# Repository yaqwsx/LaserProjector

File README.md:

# LaserProjector
Fancy driver for cheap Chinese laser galvos based on ESP32

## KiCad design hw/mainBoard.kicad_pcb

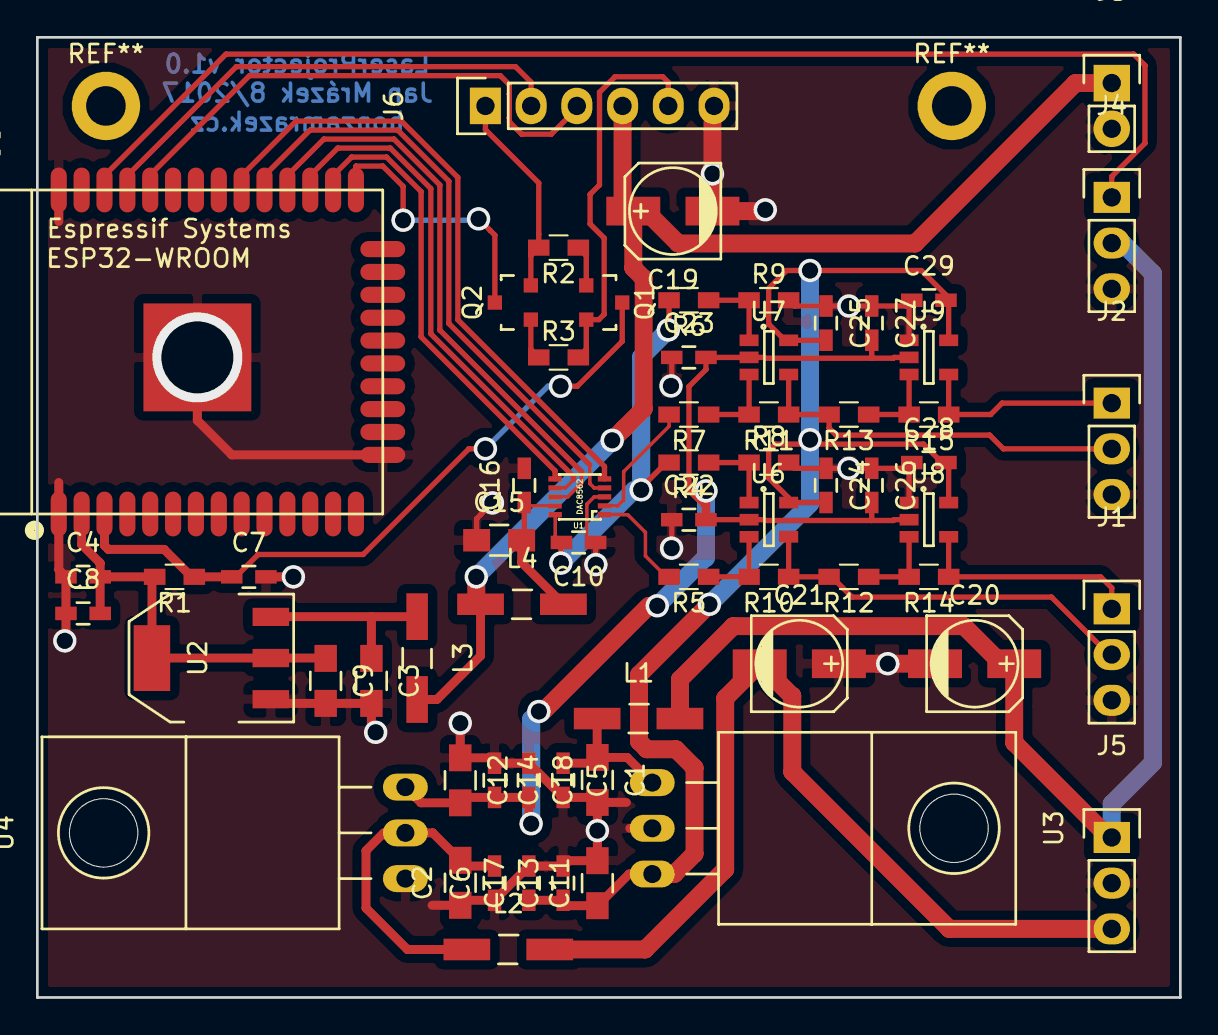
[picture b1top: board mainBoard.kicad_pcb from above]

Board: 2 copper layers, 63.5 x 53.3 mm, 65 parts (0 on the bottom side), 38 nets.

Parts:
C1, C2, C3, C9, C11, C12, C15: 10u; C_0805_HandSoldering
C4: 470n; C_0603_HandSoldering
C5, C6, C8, C13, C14, C16, C22, C23, C24, C25, C26, C27, C28, C29: 100n; C_0603_HandSoldering
C7, C17, C18: 1n; C_0603_HandSoldering
C10: 150nF; C_0603_HandSoldering
C19, C20, C21: 120u; c_elec_5x5.7
J1: Y; Pin_Header_Straight_1x03
J2: X; Pin_Header_Straight_1x03
J3: PWR_5; Pin_Header_Straight_1x02
J4: LASER; Pin_Header_Straight_1x03
J5: PWR_15; Pin_Header_Straight_1x03
J6: FTDI; Pin_Header_Straight_1x06
L1, L2, L3, L4: 33uH; Choke_SMD_1206_Handsoldering
Q1, Q2: BC817; SOT-23
R1, R2, R3, R4, R5, R6, R7: 10k; R_0603_HandSoldering
R8, R9, R10, R11, R12, R13, R14, R15: 20k; R_0603_HandSoldering
U1: DAC8562; VSSOP10
U2: AP1117; SOT-223
U3: LM7809CT; TO-220_Neutral123_Horizontal
U4: LM7909CT; TO-220_Neutral123_Horizontal
U5: ESP32-WROOM
U6, U7, U8, U9: MIC920; SOT-23-5

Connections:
+3V3: C4.2, C8.2, C9.1, R1.2, U2.2, U2.4, U5.2
+5V: C19.1, J3.1, J6.4, L3.2, L4.1
+9VA: C11.1, C13.1, C17.1, C24.2, C25.2, C28.2, C29.2, U3.3, U6.5, U7.5, U8.5, U9.5
+15V: C20.1, J4.2, J5.1, L1.2
-9VA: C12.2, C14.2, C18.2, C22.2, C23.2, C26.2, C27.2, U4.3, U6.2, U7.2, U8.2, U9.2
-15V: C21.2, J5.3, L2.2
BOOT: Q2.3, U5.25
CLR: U1.5, U5.30
DATA: U1.8, U5.28
DTR: J6.1, Q2.2, R2.2
EN: C7.1, Q1.3, R1.1, U5.3
GND: C1.2, C2.1, C3.2, C4.1, C5.2, C6.1, C7.2, C8.1, C9.2, C10.1, C11.2, C12.1, C13.2, C14.1, C15.1, C16.2, C17.2, C18.1, C19.2, C20.2, C21.1, C22.1, C23.1, C24.1, C25.1, C26.1, C27.1, C28.1, C29.1, J1.3, J2.3, J3.2, J4.3, J5.2, J6.6, R8.2, R9.2, U1.3, U2.1, U3.2, U4.1, U5.1, U5.15, U5.38, U5.39, U8.1, U9.1
LASER: J4.1, U5.36
LDAC: U1.4, U5.29
unnamed: C1.1, C5.1, L1.1, U3.1
unnamed: C2.2, C6.2, L2.1, U4.2
unnamed: C3.1, L3.1, U2.3
unnamed: C15.2, C16.1, L4.2, U1.9
unnamed: Q1.1, R2.1
unnamed: Q2.1, R3.1
unnamed: R4.1, R8.1, U6.1
unnamed: R6.1, R9.1, U7.1
unnamed: R5.1, R10.2, U6.3
unnamed: R7.1, R11.2, U7.3
unnamed: R12.1, R14.2, U8.3
unnamed: R13.1, R15.2, U9.3
RTS: J6.5, Q1.2, R3.2
RX: J6.2, U5.35
SCK: U1.7, U5.27
SIG_GROUND: C10.2, R4.2, R6.2, U1.10
SYNC: U1.6, U5.26
TX: J6.3, U5.34
XNEG: J2.1, R15.1, U9.4
XPOS: J2.2, R11.1, R13.2, U7.4
XSIG: R7.2, U1.2
YNEG: J1.1, R14.1, U8.4
YPOS: J1.2, R10.1, R12.2, U6.4
YSIG: R5.2, U1.1

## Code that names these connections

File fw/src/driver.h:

#pragma once

#include <driver/dac.h>
#include <driver/gpio.h>
#include <driver/spi_master.h>

extern "C" {
    #include <soc/spi_struct.h>
    #include <soc/spi_reg.h>

    typedef struct {
        spi_device_t *device[ 3 ];
        intr_handle_t intr;
        spi_dev_t *hw;
        spi_transaction_t *cur_trans;
        int cur_cs;
        lldesc_t *dmadesc_tx;
        lldesc_t *dmadesc_rx;
        bool no_gpio_matrix;
        int dma_chan;
        int max_transfer_sz;
    } spi_host_t;

    struct spi_device_t {
        QueueHandle_t trans_queue;
        QueueHandle_t ret_queue;
        spi_device_interface_config_t cfg;
        spi_host_t *host;
    };
}

struct IntDacDriver {
    IntDacDriver( gpio_num_t laserPin )
        : _lPin( laserPin )
    { }

    ~IntDacDriver() {
        stop();
    }

    void start() {
        dac_output_enable( DAC_CHANNEL_1 ); // GPIO 25
        dac_output_enable( DAC_CHANNEL_2 ); // GPIO 26
        gpio_set_direction( _lPin, GPIO_MODE_OUTPUT );
        gpio_set_level( _lPin, 0 );
    }

    void stop() {
        gpio_set_level( _lPin, 0 );
    }

    void show( ImgPoint p ) {
        dac_output_voltage( DAC_CHANNEL_1, 128 + ( p.x / 255 ) );
        dac_output_voltage( DAC_CHANNEL_2, 128 + ( p.y / 255 ) );
        gpio_set_level( _lPin, p.l > 0 );
    }

    gpio_num_t _lPin;
};

struct Dac8562Driver {
    Dac8562Driver( gpio_num_t din, gpio_num_t sck, gpio_num_t sync,
        gpio_num_t clr, gpio_num_t ldac, gpio_num_t laserPin )
    : _ldac( ldac ),
      _lPin( laserPin )
    {
        gpio_set_direction( clr, GPIO_MODE_OUTPUT );
        gpio_set_level( clr, 1 );

        gpio_set_direction( _ldac, GPIO_MODE_OUTPUT );
        gpio_set_level( _ldac, 1 );

        gpio_set_direction( _lPin, GPIO_MODE_OUTPUT );
        gpio_set_level( _lPin, 0 );

        spi_bus_config_t buscfg;
        buscfg.miso_io_num = -1;
        buscfg.mosi_io_num = din;
        buscfg.sclk_io_num = sck;
        buscfg.quadhd_io_num = -1;
        buscfg.quadwp_io_num = -1;
        buscfg.max_transfer_sz = 0;

        spi_device_interface_config_t devcfg;
        memset( &devcfg, 0, sizeof( devcfg ) );
        devcfg.mode = 1; // Falling edge of SCK
        devcfg.clock_speed_hz = 10'000'000;
        devcfg.spics_io_num = sync;
        devcfg.flags = SPI_DEVICE_HALFDUPLEX;
        devcfg.queue_size = 8;

        esp_err_t ret;

        ret = spi_bus_initialize( HSPI_HOST, &buscfg, 0 /* do not use DMA */ );
        assert( ret == ESP_OK );
        ret = spi_bus_add_device( HSPI_HOST, &devcfg, &_spi );
        assert( ret == ESP_OK );
    }

    void send( uint32_t cmd ) {
        spi_transaction_t t;
        t.flags = SPI_TRANS_USE_TXDATA;
        t.command = 0;
        t.address = 0;
        t.length = 24;
        t.rxlength = 0;
        t.tx_data[ 0 ] = ( cmd >> 16 ) & 0xFF;
        t.tx_data[ 1 ] = ( cmd >> 8  ) & 0xFF;
        t.tx_data[ 2 ] = ( cmd >> 0  ) & 0xFF;
        auto ret = spi_device_transmit( _spi, &t );
        assert( ret == ESP_OK );
    }

    void sendFast( uint32_t data ) {
        //Reset SPI peripheral
        _spi->host->hw->dma_conf.val |= SPI_OUT_RST|SPI_IN_RST|SPI_AHBM_RST|SPI_AHBM_FIFO_RST;
        _spi->host->hw->dma_out_link.start=0;
        _spi->host->hw->dma_in_link.start=0;
        _spi->host->hw->dma_conf.val &= ~(SPI_OUT_RST|SPI_IN_RST|SPI_AHBM_RST|SPI_AHBM_FIFO_RST);
        _spi->host->hw->dma_conf.out_data_burst_en=1;
        //Set up QIO/DIO if needed
        _spi-> host->hw->ctrl.val &= ~(SPI_FREAD_DUAL|SPI_FREAD_QUAD|SPI_FREAD_DIO|SPI_FREAD_QIO);
        _spi->host->hw->user.val &= ~(SPI_FWRITE_DUAL|SPI_FWRITE_QUAD|SPI_FWRITE_DIO|SPI_FWRITE_QIO);

        data = ( data & 0xFF )     << 16 |
               ( data & 0xFF00 )   << 0  |
               ( data & 0xFF0000 ) >> 16 ;
        _spi->host->hw->data_buf[ 0 ] = data;
        _spi->host->hw->user.usr_mosi_highpart = 0;

        _spi->host->hw->mosi_dlen.usr_mosi_dbitlen = 23;
        _spi->host->hw->miso_dlen.usr_miso_dbitlen = 0;

        _spi->host->hw->user.usr_mosi = 1;
        _spi->host->hw->cmd.usr = 1;
        while( _spi->host->hw->cmd.usr );
    }

    void start() {
        // Send as a side effect initializes SPI bus, so sendFast doesn't have to
        send( cmd( 0b111, 0, 1 ) ); // enable internal reference
        send( cmd( 0b110, 0 , 0 ) ); // enable LDAC pin
    }

    void stop() {

    }

    static uint32_t cmd( uint8_t c, uint8_t a, uint16_t d ) {
        return ( static_cast< uint32_t >( c ) & 0x7 ) << 19 |
               ( static_cast< uint32_t >( a ) & 0x7 ) << 16 |
               d;
    }

    void show( ImgPoint p ) {
        uint16_t x = static_cast< int32_t >( p.x ) + 32768;
        uint16_t y = static_cast< int32_t >( p.y ) + 32768;
        sendFast( cmd( 0, 0, x ) );
        sendFast( cmd( 0, 1, y ) );
        gpio_set_level( _ldac, 0 );
        gpio_set_level( _ldac, 1 );
        gpio_set_level( _lPin, 1 );
    }


    static void onFinishedTransfer( spi_transaction_t* t ) {
        uint32_t usr = reinterpret_cast< uint32_t >( t->user );
        auto update = usr >> 16;
        if ( update == 0xFFFF )
            return;
        auto pin = static_cast< gpio_num_t >( update );
        gpio_set_level( pin, 0 );
        gpio_set_level( pin, 1 );

        auto laserPin = static_cast< gpio_num_t >( usr & 0xFF );
        auto level = ( usr >> 8 ) & 0xFF;
        gpio_set_level( laserPin, level );
    }

    gpio_num_t _ldac, _lPin;
    spi_device_handle_t _spi;
};

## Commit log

2017-08-01 Initial commit of work-in-progress
2017-08-01 Finalize transformations
2017-08-01 Move transformations from interrupt to a task
2017-08-01 Initial schematic for the board
2017-08-02 Initial routing
2017-08-06 Add driver for new board
2017-08-06 Final touch on the board
2017-09-02 Read svg path from file.
